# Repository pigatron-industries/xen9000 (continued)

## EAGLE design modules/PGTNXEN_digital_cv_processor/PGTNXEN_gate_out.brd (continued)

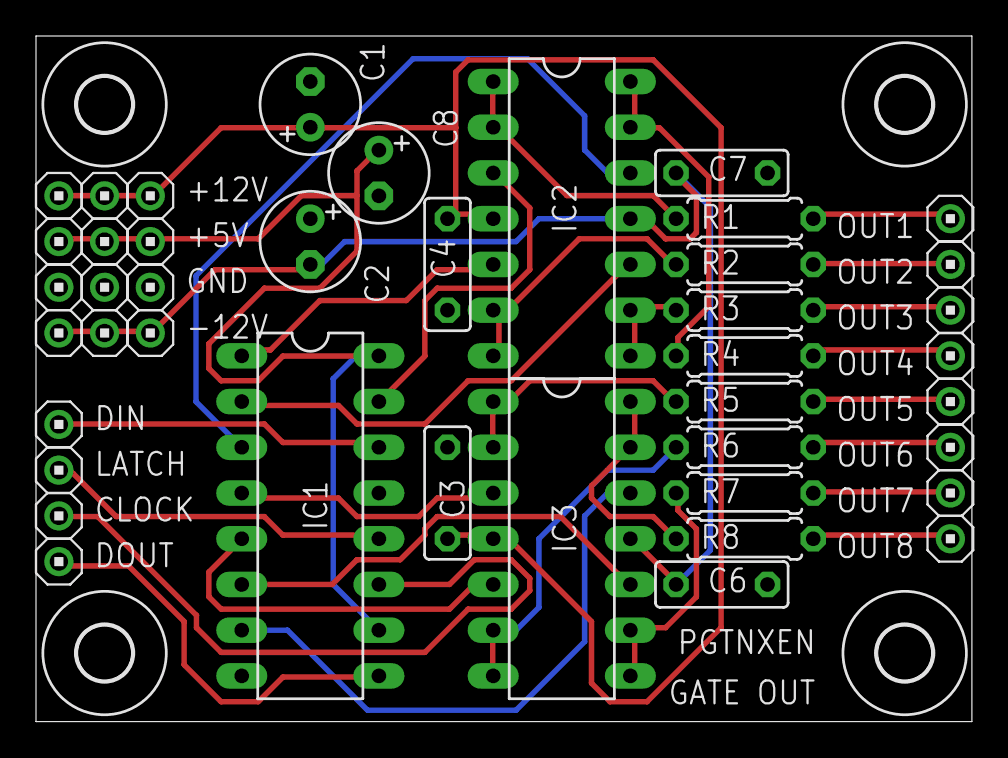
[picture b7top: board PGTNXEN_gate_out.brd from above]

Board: 2 copper layers, 52.0 x 38.1 mm, 47 parts (1 on the bottom side), 32 nets.

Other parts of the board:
U$1, U$2, U$3, U$4: STANDOFF/3.0
U$5: PIGATRON-LOGO

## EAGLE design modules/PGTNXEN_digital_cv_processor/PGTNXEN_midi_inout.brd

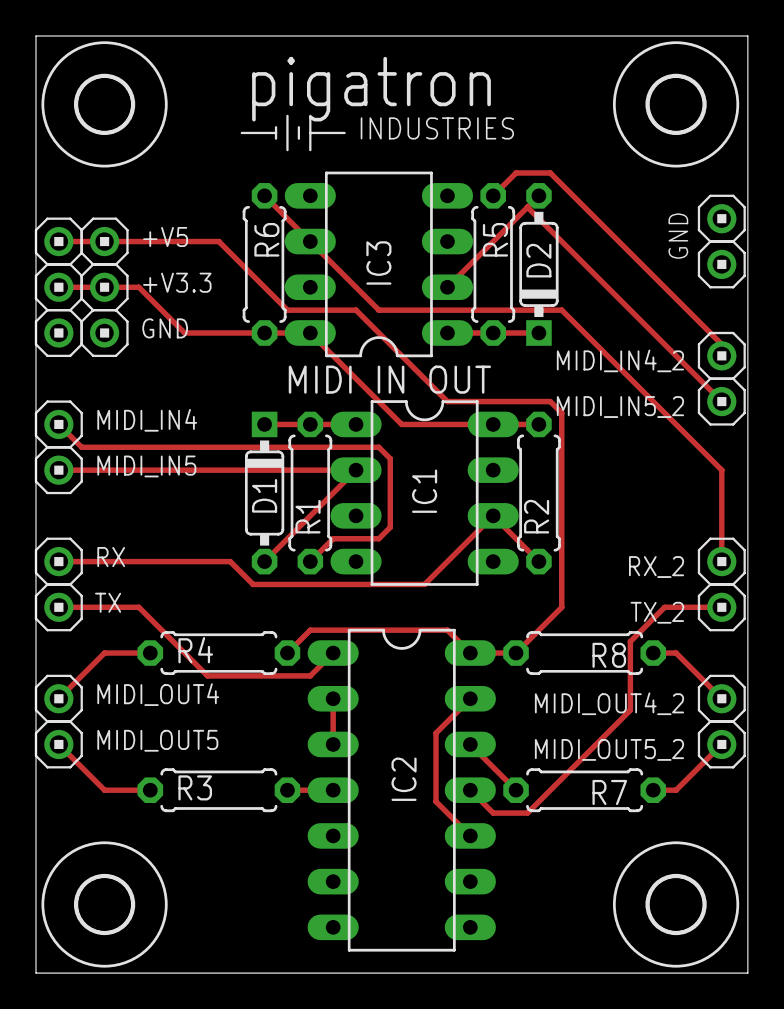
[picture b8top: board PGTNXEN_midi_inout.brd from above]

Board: 2 copper layers, 39.5 x 52.1 mm, 38 parts (0 on the bottom side), 21 nets.

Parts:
+V3.3, +V3.3_2, +V5, +V5_1: HEADER/MALE/01
D1, D2: DO35-7
GND, GND1, GND2, GND3: HEADER/MALE/01
IC1, IC3: H11L1; DIL08
IC2: 40106N; DIL14
MIDI_IN4, MIDI_IN4_2, MIDI_IN5, MIDI_IN5_2: HEADER/MALE/01
MIDI_OUT4, MIDI_OUT4_2, MIDI_OUT5, MIDI_OUT5_2: HEADER/MALE/01
R1, R2, R3, R4, R5, R6, R7, R8: 220R; RESISTOR/7.5
RX: HEADER/MALE/01
RX_2: HEADER/MALE/01
TX: HEADER/MALE/01
TX_2: HEADER/MALE/01
U$1, U$2, U$3, U$4: STANDOFF/3.0
U$5: PIGATRON-LOGO

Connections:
GND: GND.1, GND1.1, GND2.1, GND3.1, IC1.7, IC2.7, IC3.7
unnamed: D1.C, IC1.1, R1.2
unnamed: MIDI_IN4.1, R1.1
unnamed: D1.A, IC1.2, MIDI_IN5.1
unnamed: IC1.6, R2.1, RX.1
unnamed: IC2.11, TX_2.1
unnamed: IC2.1, TX.1
unnamed: IC2.2, IC2.3
unnamed: IC2.4, R3.2
unnamed: MIDI_OUT5.1, R3.1
unnamed: MIDI_OUT4.1, R4.1
unnamed: MIDI_IN4_2.1, R5.1
unnamed: D2.C, IC3.1, R5.2
unnamed: D2.A, IC3.2, MIDI_IN5_2.1
unnamed: IC3.6, R6.1, RX_2.1
unnamed: +V3.3.1, +V3.3_2.1, IC1.8, IC3.8, R2.2, R6.2
unnamed: IC2.10, IC2.13
unnamed: IC2.12, R7.2
unnamed: MIDI_OUT5_2.1, R7.1
unnamed: +V5.1, +V5_1.1, IC2.14, R4.2, R8.2
unnamed: MIDI_OUT4_2.1, R8.1
